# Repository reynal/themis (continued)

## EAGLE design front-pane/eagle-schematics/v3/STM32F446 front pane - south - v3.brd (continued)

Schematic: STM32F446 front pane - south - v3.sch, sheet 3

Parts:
C83, C84, C87, C88, C89, C90, C107, C108, C121, C122, C123, C124, C125, C126: 10u; CPOL2917
C85, C86, C99, C100, C101, C102, C115, C116, C119, C120, C135, C136, C137, C138: 100n; 0805-CAP
C91, C92, C93, C94, C95, C96, C97, C98, C103, C104, C105, C106, C109, C110, C111, C112, C113, C114, C117, C118, C127, C128, C129, C130, C131, C132, C133, C134, C139, C140, C141, C142: 10n; 0805-CAP
D9, D10: CZXR-80RGB03-A; LED4-2.0-D8.0MM
IC22, IC23, IC24, IC25, IC26, IC27, IC28, IC29, IC30, IC31, IC32, IC33: NEOPIXEL-TLC59731DR; SOIC127P600X175-8N
MCP_011, MCP_100: MCP23017; SOIC-28
R130, R131, R132, R133: 1k; R0805
R134, R135, R136, R137, R138, R139, R140, R141, R142, R143, R144, R145, R162, R163, R164, R165, R166, R167, R168, R169, R184, R185, R186, R187, R188, R189, R190, R191, R192, R193, R194, R195: 470; 1206
R146, R147, R148, R150, R151, R152, R154, R155, R156, R158, R159, R160, R170, R171, R172, R174, R175, R176, R178, R179, R180, R181, R182, R183, R196, R197, R198, R200, R201, R202, R204, R205, R206, R208, R209, R210: 100; 1206
R149, R153, R157, R161, R173, R177, R199, R203, R207, R211: 10k; 1206
S14, S15, S16, S17, S18, S19, S20, S21, S22, S23: ENCODER-RGB-SWITCH-NO_NUT; ENCODER_LED_3
SW9, SW10: B3F-1000

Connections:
3V3: C83.+, C84.+, C85.1, C86.1, C87.+, C88.+, C89.+, C90.+, C99.1, C100.1, C101.1, C102.1, C107.+, C108.+, C115.1, C116.1, C119.1, C120.1, C121.+, C122.+, C123.+, C124.+, C125.+, C126.+, C135.1, C136.1, C137.1, C138.1, D9.2 (+), D10.2 (+), IC22.8 (VCC), IC23.8 (VCC), IC24.8 (VCC), IC25.8 (VCC), IC26.8 (VCC), IC27.8 (VCC), IC28.8 (VCC), IC29.8 (VCC), IC30.8 (VCC), IC31.8 (VCC), IC32.8 (VCC), IC33.8 (VCC), MCP_011.9 (VDD), MCP_011.15 (A0), MCP_011.16 (A1), MCP_100.9 (VDD), MCP_100.17 (A2), R130.2, R131.2, R132.2, R133.2, S14.5 (+), S15.5 (+), S16.5 (+), S17.5 (+), S18.5 (+), S19.5 (+), S20.5 (+), S21.5 (+), S22.5 (+), S23.5 (+); also elsewhere on the board
GND: C83.-, C84.-, C85.2, C86.2, C87.-, C88.-, C89.-, C90.-, C91.1, C92.1, C93.1, C94.1, C95.1, C96.1, C97.1, C98.1, C99.2, C100.2, C101.2, C102.2, C103.2, C104.2, C105.2, C106.2, C107.-, C108.-, C109.1, C110.1, C111.1, C112.1, C113.1, C114.1, C115.2, C116.2, C117.2, C118.2, C119.2, C120.2, C121.-, C122.-, C123.-, C124.-, C125.-, C126.-, C127.1, C128.1, C129.1, C130.1, C131.1, C132.1, C133.1, C134.1, C135.2, C136.2, C137.2, C138.2, C139.2, C140.2, C141.2, C142.2, IC22.4 (GND), IC23.4 (GND), IC24.4 (GND), IC25.4 (GND), IC26.4 (GND), IC27.4 (GND), IC28.4 (GND), IC29.4 (GND), IC30.4 (GND), IC31.4 (GND), IC32.4 (GND), IC33.4 (GND), MCP_011.10 (VSS), MCP_011.17 (A2), MCP_100.10 (VSS), MCP_100.15 (A0), MCP_100.16 (A1), R149.2, R153.2, R157.2, R161.2, R173.2, R177.2, R199.2, R203.2, R207.2, R211.2, S14.C, S15.C, S16.C, S17.C, S18.C, S19.C, S20.C, S21.C, S22.C, S23.C, SW9.1, SW9.2, SW10.1, SW10.2; also elsewhere on the board
GPA0_31: MCP_011.21 (GPA0), R140.1, S17.A
GPA0_32: MCP_100.21 (GPA0), R162.1, SW9.3, SW9.4
GPA1_31: MCP_011.22 (GPA1), R141.1, S17.B
GPA1_32: MCP_100.22 (GPA1), R192.1, R199.1, S20.3 (SW)
GPA2_31: MCP_011.23 (GPA2), R145.1, R161.1, S17.3 (SW)
GPA2_32: MCP_100.23 (GPA2), R185.1, S20.B
GPA3_31: MCP_011.24 (GPA3), R163.1, SW10.3, SW10.4
GPA3_32: MCP_100.24 (GPA3), R184.1, S20.A
GPA4_31: MCP_011.25 (GPA4), R144.1, R157.1, S16.3 (SW)
GPA4_32: MCP_100.25 (GPA4), R193.1, R203.1, S21.3 (SW)
GPA5_31: MCP_011.26 (GPA5), R138.1, S16.A
GPA5_32: MCP_100.26 (GPA5), R187.1, S21.B
GPA6_31: MCP_011.27 (GPA6), R139.1, S16.B
GPA6_32: MCP_100.27 (GPA6), R186.1, S21.A
GPA7_31: MCP_011.28 (GPA7), R168.1, R173.1, S18.3 (SW)
GPA7_32: MCP_100.28 (GPA7), R194.1, R207.1, S22.3 (SW)
GPB0_31: MCP_011.1 (GPB0), R165.1, S18.B
GPB0_32: MCP_100.1 (GPB0), R189.1, S22.B
GPB1_31: MCP_011.2 (GPB1), R164.1, S18.A
GPB1_32: MCP_100.2 (GPB1), R188.1, S22.A
GPB2_31: MCP_011.3 (GPB2), R169.1, R177.1, S19.3 (SW)
GPB2_32: MCP_100.3 (GPB2), R191.1, S23.B
GPB3_31: MCP_011.4 (GPB3), R167.1, S19.B
GPB3_32: MCP_100.4 (GPB3), R190.1, S23.A
GPB4_31: MCP_011.5 (GPB4), R166.1, S19.A
GPB4_32: MCP_100.5 (GPB4), R195.1, R211.1, S23.3 (SW)
GPB5_31: MCP_011.6 (GPB5), R134.1, S14.A
GPB5_32: MCP_100.6 (GPB5), R136.1, S15.A
GPB6_31: MCP_011.7 (GPB6), R135.1, S14.B
GPB6_32: MCP_100.7 (GPB6), R137.1, S15.B
GPB7_31: MCP_011.8 (GPB7), R142.1, R149.1, S14.3 (SW)
GPB7_32: MCP_100.8 (GPB7), R143.1, R153.1, S15.3 (SW)
I2C2_SCL: MCP_011.12 (SCL), MCP_100.12 (SCL), R132.1, R133.1; also elsewhere on the board
I2C2_SDA: MCP_011.13 (SDA), MCP_100.13 (SDA), R130.1, R131.1; also elsewhere on the board
INTA_31: MCP_011.20 (INTA); also elsewhere on the board
INTA_32: MCP_100.20 (INTA); also elsewhere on the board
INTB_31: MCP_011.19 (INTB); also elsewhere on the board
INTB_32: MCP_100.19 (INTB); also elsewhere on the board
unnamed: R158.2, S17.1 (-R)
unnamed: R159.2, S17.2 (-G)
unnamed: R160.2, S17.4 (-B)
unnamed: IC25.1 (OUT0), R158.1
unnamed: IC25.2 (OUT1), R159.1
unnamed: IC25.3 (OUT2), R160.1
unnamed: C97.2, R140.2
unnamed: C98.2, R141.2
unnamed: C106.1, R145.2
unnamed: R154.2, S16.1 (-R)
unnamed: R155.2, S16.2 (-G)
unnamed: R156.2, S16.4 (-B)
unnamed: IC24.1 (OUT0), R154.1
unnamed: IC24.2 (OUT1), R155.1
unnamed: IC24.3 (OUT2), R156.1
unnamed: C95.2, R138.2
unnamed: C96.2, R139.2
unnamed: C105.1, R144.2
unnamed: R150.2, S15.1 (-R)
unnamed: R151.2, S15.2 (-G)
unnamed: R152.2, S15.4 (-B)
unnamed: IC23.1 (OUT0), R150.1
unnamed: IC23.2 (OUT1), R151.1
unnamed: IC23.3 (OUT2), R152.1
unnamed: C93.2, R136.2
unnamed: C94.2, R137.2
unnamed: C104.1, R143.2
unnamed: R146.2, S14.1 (-R)
unnamed: R147.2, S14.2 (-G)
unnamed: R148.2, S14.4 (-B)
unnamed: IC22.1 (OUT0), R146.1
unnamed: IC22.2 (OUT1), R147.1
unnamed: IC22.3 (OUT2), R148.1
unnamed: C91.2, R134.2
unnamed: C92.2, R135.2
unnamed: C103.1, R142.2
unnamed: R174.2, S19.1 (-R)
unnamed: R175.2, S19.2 (-G)
unnamed: R176.2, S19.4 (-B)
unnamed: IC29.1 (OUT0), R174.1
unnamed: IC29.2 (OUT1), R175.1
unnamed: IC29.3 (OUT2), R176.1
unnamed: C111.2, R166.2
unnamed: C112.2, R167.2
unnamed: C118.1, R169.2
unnamed: IC27.1 (OUT0), R181.1
unnamed: IC27.2 (OUT1), R182.1
unnamed: IC27.3 (OUT2), R183.1
unnamed: C114.2, R163.2
unnamed: R170.2, S18.1 (-R)
unnamed: R171.2, S18.2 (-G)
unnamed: R172.2, S18.4 (-B)
unnamed: IC28.1 (OUT0), R170.1
unnamed: IC28.2 (OUT1), R171.1
unnamed: IC28.3 (OUT2), R172.1
unnamed: C109.2, R164.2
unnamed: C110.2, R165.2
unnamed: C117.1, R168.2
unnamed: R208.2, S23.1 (-R)
unnamed: R209.2, S23.2 (-G)
unnamed: R210.2, S23.4 (-B)
unnamed: IC33.1 (OUT0), R208.1
unnamed: IC33.2 (OUT1), R209.1
unnamed: IC33.3 (OUT2), R210.1
unnamed: C133.2, R190.2
unnamed: C134.2, R191.2
unnamed: C142.1, R195.2
unnamed: R204.2, S22.1 (-R)
unnamed: R205.2, S22.2 (-G)
unnamed: R206.2, S22.4 (-B)
unnamed: IC32.1 (OUT0), R204.1
unnamed: IC32.2 (OUT1), R205.1
unnamed: IC32.3 (OUT2), R206.1
unnamed: C131.2, R188.2
unnamed: C132.2, R189.2
unnamed: C141.1, R194.2
unnamed: R200.2, S21.1 (-R)
unnamed: R201.2, S21.2 (-G)
unnamed: R202.2, S21.4 (-B)
unnamed: IC31.1 (OUT0), R200.1
unnamed: IC31.2 (OUT1), R201.1
unnamed: IC31.3 (OUT2), R202.1
unnamed: C129.2, R186.2
unnamed: C130.2, R187.2
unnamed: C140.1, R193.2
unnamed: D10.1 (R), R183.2
unnamed: D10.4 (B), R182.2
unnamed: D10.3 (G), R181.2
unnamed: R196.2, S20.1 (-R)
unnamed: R197.2, S20.2 (-G)
unnamed: R198.2, S20.4 (-B)
unnamed: IC30.1 (OUT0), R196.1
unnamed: IC30.2 (OUT1), R197.1
unnamed: IC30.3 (OUT2), R198.1
unnamed: C127.2, R184.2
unnamed: C128.2, R185.2
unnamed: C139.1, R192.2
unnamed: IC26.1 (OUT0), R178.1
unnamed: IC26.2 (OUT1), R179.1
unnamed: IC26.3 (OUT2), R180.1
unnamed: C113.2, R162.2
unnamed: D9.1 (R), R180.2
unnamed: D9.4 (B), R179.2
unnamed: D9.3 (G), R178.2
PIXEL_48: IC33.6 (SDI); also elsewhere on the board
PIXEL_51: IC25.5 (SDO), IC27.6 (SDI)
PIXEL_52: IC24.6 (SDI), IC27.5 (SDO)
PIXEL_53: IC24.5 (SDO), IC28.6 (SDI)
PIXEL_54: IC23.5 (SDO); also elsewhere on the board
PIXEL_55: IC22.5 (SDO), IC23.6 (SDI)
PIXEL_56: IC22.6 (SDI), IC29.5 (SDO)
PIXEL_57: IC28.5 (SDO), IC29.6 (SDI)
PIXEL_61: IC32.6 (SDI), IC33.5 (SDO)
PIXEL_62: IC31.6 (SDI), IC32.5 (SDO)
PIXEL_63: IC30.6 (SDI), IC31.5 (SDO)
PIXEL_64: IC26.6 (SDI), IC30.5 (SDO)
RST: MCP_011.18 (!RESET), MCP_100.18 (!RESET); also elsewhere on the board
SPI3_MOSI: IC25.6 (SDI); also elsewhere on the board

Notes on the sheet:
RGB ENCODER 51
RGB ENCODER 53
RGB ENCODER 54
RGB ENCODER 55
RGB ENCODER 56
RGB ENCODER 57
RGB ENCODER 61
RGB ENCODER 62
RGB ENCODER 63
RGB ENCODER 64
SWITCH RGB 52
SWITCH RGB 65

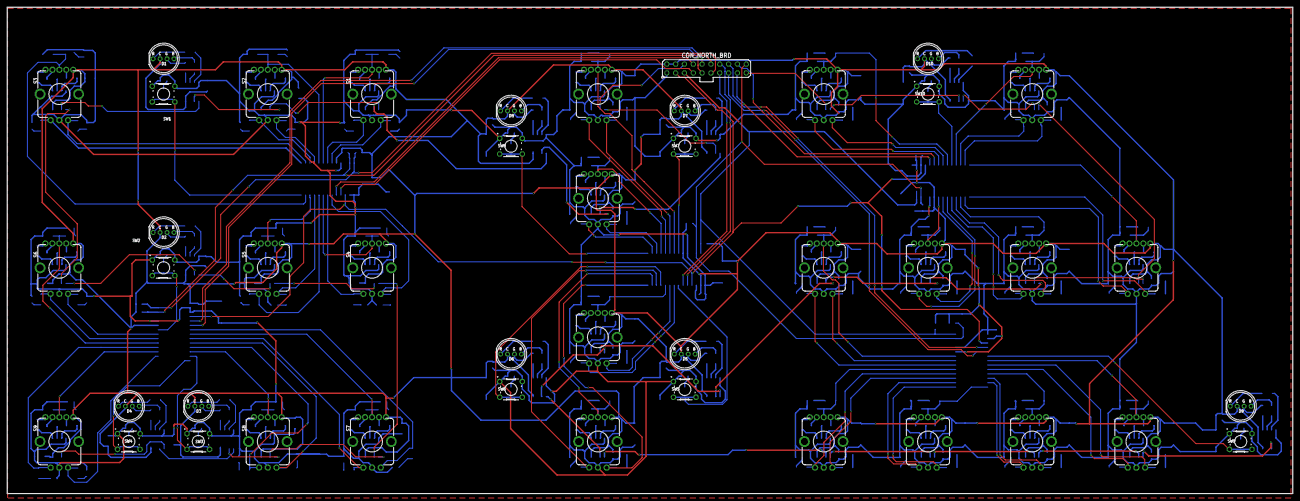
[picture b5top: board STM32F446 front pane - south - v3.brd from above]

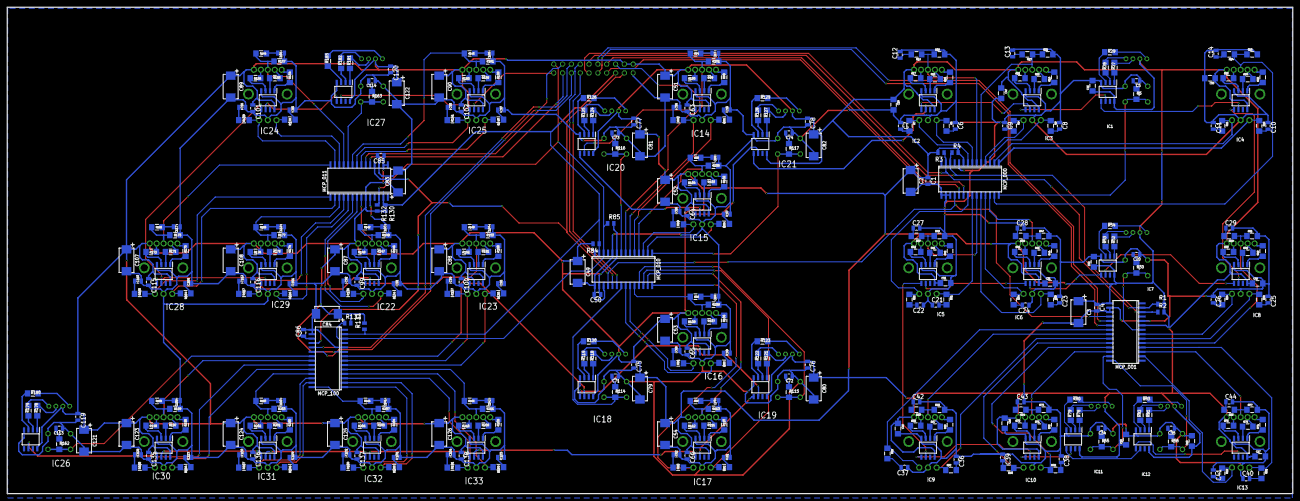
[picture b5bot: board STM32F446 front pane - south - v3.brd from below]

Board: 2 copper layers, 370.0 x 140.0 mm, 435 parts (391 on the bottom side), 406 nets.

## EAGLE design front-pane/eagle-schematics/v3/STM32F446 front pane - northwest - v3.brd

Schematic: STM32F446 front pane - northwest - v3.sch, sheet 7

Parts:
C1, C2, C5, C6, C7, C10, C11, C12, C15: 10n; 0805-CAP
C3, C8, C13: 10u; CPOL2917
C4, C9, C14: 100n; 0805-CAP
ENC_01, ENC_02, ENC_3: ENCODER-RGB-SWITCH-NO_NUT; ENCODER_LED_3
PIXEL_01, PIXEL_02, PIXEL_03: NEOPIXEL-TLC59731DR; SOIC127P600X175-8N
R1, R2, R7, R8, R9, R14, R15, R16, R21: 470; 1206
R3, R4, R5, R10, R11, R12, R17, R18, R19: 100; 1206
R6, R13, R20: 10k; 1206
TFT_EXT_2: MA06-2

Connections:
3V3: C3.+, C4.1, C8.+, C9.1, C13.+, C14.1, ENC_01.5 (+), ENC_02.5 (+), ENC_3.5 (+), PIXEL_01.8 (VCC), PIXEL_02.8 (VCC), PIXEL_03.8 (VCC), TFT_EXT_2.1
ENC_01_A: ENC_01.A, R15.1, TFT_EXT_2.3
ENC_01_B: ENC_01.B, R16.1, TFT_EXT_2.5
ENC_01_SW: ENC_01.3 (SW), R20.1, R21.1, TFT_EXT_2.6
ENC_02_A: ENC_02.A, R8.1, TFT_EXT_2.11
ENC_02_B: ENC_02.B, R9.1, TFT_EXT_2.12
ENC_02_SW: ENC_02.3 (SW), R13.1, R14.1, TFT_EXT_2.4
ENC_03_A: ENC_3.A, R1.1, TFT_EXT_2.10
ENC_03_B: ENC_3.B, R2.1, TFT_EXT_2.8
ENC_03_SW: ENC_3.3 (SW), R6.1, R7.1, TFT_EXT_2.2
GND: C1.1, C2.1, C3.-, C4.2, C5.2, C6.1, C7.1, C8.-, C9.2, C10.2, C11.1, C12.1, C13.-, C14.2, C15.2, ENC_01.C, ENC_02.C, ENC_3.C, PIXEL_01.4 (GND), PIXEL_02.4 (GND), PIXEL_03.4 (GND), R6.2, R13.2, R20.2, TFT_EXT_2.7
unnamed: ENC_01.1 (-R), R17.2
unnamed: ENC_01.2 (-G), R18.2
unnamed: ENC_01.4 (-B), R19.2
unnamed: PIXEL_01.1 (OUT0), R17.1
unnamed: PIXEL_01.2 (OUT1), R18.1
unnamed: PIXEL_01.3 (OUT2), R19.1
unnamed: C11.2, R15.2
unnamed: C12.2, R16.2
unnamed: C15.1, R21.2
unnamed: ENC_02.1 (-R), R10.2
unnamed: ENC_02.2 (-G), R11.2
unnamed: ENC_02.4 (-B), R12.2
unnamed: PIXEL_02.1 (OUT0), R10.1
unnamed: PIXEL_02.2 (OUT1), R11.1
unnamed: PIXEL_02.3 (OUT2), R12.1
unnamed: C6.2, R8.2
unnamed: C7.2, R9.2
unnamed: C10.1, R14.2
unnamed: ENC_3.1 (-R), R3.2
unnamed: ENC_3.2 (-G), R4.2
unnamed: ENC_3.4 (-B), R5.2
unnamed: PIXEL_03.1 (OUT0), R3.1
unnamed: PIXEL_03.2 (OUT1), R4.1
unnamed: PIXEL_03.3 (OUT2), R5.1
unnamed: C1.2, R1.2
unnamed: C2.2, R2.2
unnamed: C5.1, R7.2
PIXEL_02: PIXEL_01.6 (SDI), PIXEL_02.5 (SDO)
PIXEL_03: PIXEL_02.6 (SDI), PIXEL_03.5 (SDO)
PIXEL_IN: PIXEL_03.6 (SDI), TFT_EXT_2.9

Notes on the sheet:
TFT EXTENSION
RGB ENCODER

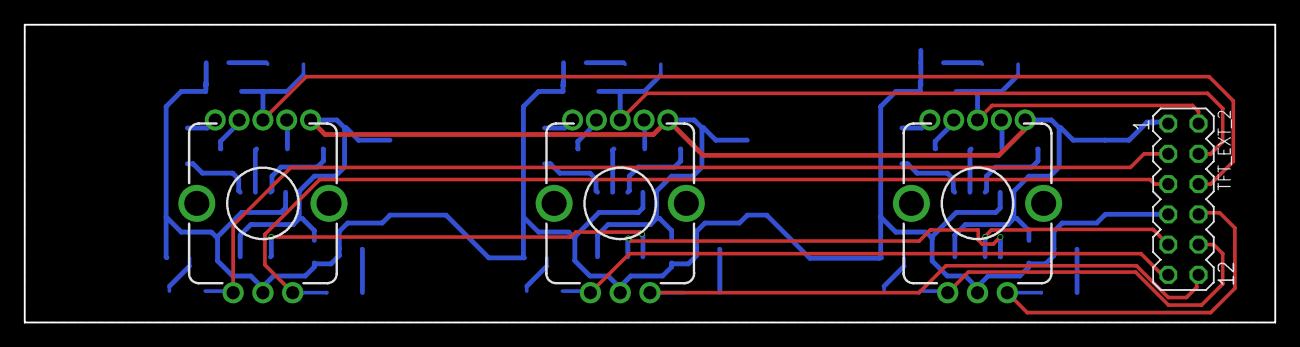
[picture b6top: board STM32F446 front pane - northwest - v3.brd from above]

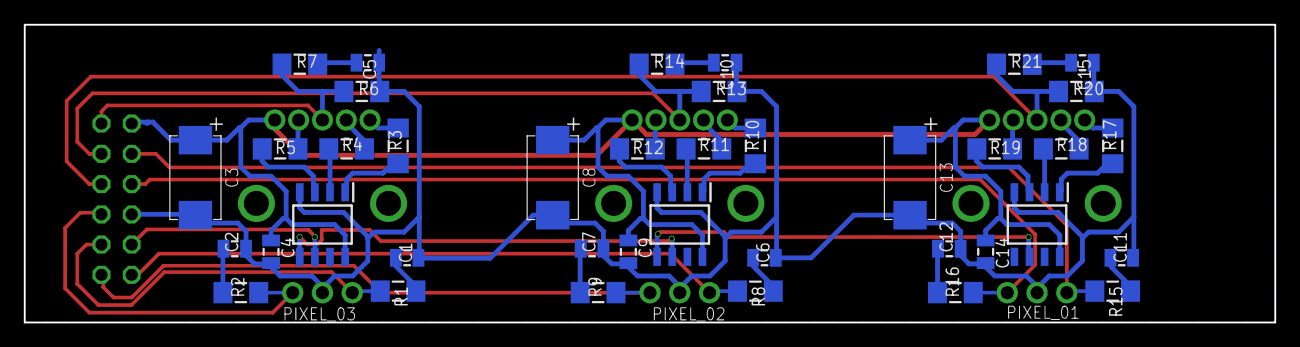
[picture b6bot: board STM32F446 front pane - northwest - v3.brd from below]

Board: 2 copper layers, 105.0 x 25.0 mm, 43 parts (39 on the bottom side), 41 nets.

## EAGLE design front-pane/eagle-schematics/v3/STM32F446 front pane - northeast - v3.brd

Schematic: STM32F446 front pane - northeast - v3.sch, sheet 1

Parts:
0V/5V: SUPPLY; MA04-1
AIN: MA04-1
ANALOG: UART_ANALOG; MA03-1
C1, C6, C7, C8, C9, C10: 0.1uF; C0805
C2: 2.2uF; C0805
C3: 10u; CPOL2917
C4: 100 uF; CPOL2917
C5: 1u; C1206
C11: 1.0uF; C0805
CON_STH_BRD: SOUTH; MA10-2
DISCO: UART_DISCO; MA03-1
F446: STM32F446RCT7; QFP50P1200X1200X160-64N
L1: 1 uH; L0805
LD_3V: LED_3V3; 0805-LED
LD_5V: LED_5V; 0603-LED
LD_GR: LED-0805; 0805-LED
MIDI: UART_MIDI; MA03-1
NRST: SWITCH-SKRKAEE020; SKRKAEE020
R1, R5: 1k; R0805
R2: 100k; R0805
R3: 10K; R0805
R4: 1; R0805
R6: 470; R0805
REG: TLV75533PDBVR; SOT95P280X145-5N
STLINK: STLINK; MA03-2

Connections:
3V3: C4.+, C6.2, C7.2, C8.2, C9.2, C10.2, C11.2, CON_STH_BRD.2, CON_STH_BRD.4, F446.1 (VBAT), F446.13 (VDDA/VREF+), F446.19 (VDD_4), F446.32 (VDD_1), F446.48 (VDD_2), F446.64 (VDD_3), L1.2, R2.1, R5.1, STLINK.1; also elsewhere on the board
5V: 0V/5V.3, 0V/5V.4, C3.+, C5.2, R6.1, REG.1 (IN), REG.3 (EN)
ADC1_IN1: AIN.4, F446.15 (PA1)
ADC1_IN4: AIN.3, F446.20 (PA4)
ADC1_IN10: AIN.2, F446.8 (PC0)
BOOT1: F446.60 (BOOT0), R3.1
GND: 0V/5V.1, 0V/5V.2, AIN.1, ANALOG.1, C1.1, C2.1, C3.-, C4.-, C5.1, C6.1, C7.1, C8.1, C9.1, C10.1, C11.1, CON_STH_BRD.1, DISCO.1, F446.12 (VSSA/VREF-), F446.18 (VSS_4), F446.31 (VSS_1), F446.47 (VSS_2), F446.63 (VSS_3), LD_3V.C, LD_5V.C, LD_GR.C, MIDI.1, NRST.1, R3.2, REG.2 (GND), STLINK.5; also elsewhere on the board
GPIO_EXTI0: F446.5 (PH0-OSC_IN); also elsewhere on the board
GPIO_EXTI1: CON_STH_BRD.17, F446.27 (PB1)
GPIO_EXTI2: F446.10 (PC2); also elsewhere on the board
GPIO_EXTI3: F446.11 (PC3); also elsewhere on the board
GPIO_EXTI4: F446.24 (PC4); also elsewhere on the board
GPIO_EXTI5: F446.25 (PC5); also elsewhere on the board
GPIO_EXTI6: CON_STH_BRD.16, F446.37 (PC6)
GPIO_EXTI7: CON_STH_BRD.13, F446.38 (PC7)
GPIO_EXTI8: CON_STH_BRD.14, F446.39 (PC8)
GPIO_EXTI9: CON_STH_BRD.9, F446.42 (PA9)
GPIO_EXTI10: CON_STH_BRD.10, F446.43 (PA10)
GPIO_EXTI11: CON_STH_BRD.7, F446.44 (PA11)
GPIO_EXTI12: CON_STH_BRD.8, F446.45 (PA12)
GPIO_EXTI13: F446.2 (PC13); also elsewhere on the board
GPIO_EXTI14: CON_STH_BRD.18, F446.35 (PB14)
GPIO_EXTI15: CON_STH_BRD.15, F446.36 (PB15)
I2C1_SCL: F446.61 (PB8); also elsewhere on the board
I2C1_SDA: F446.62 (PB9); also elsewhere on the board
I2C2_SCL: CON_STH_BRD.20, F446.29 (PB10)
I2C2_SDA: CON_STH_BRD.5, F446.53 (PC12)
I2C3_SCL: CON_STH_BRD.12, F446.41 (PA8)
I2C3_SDA: CON_STH_BRD.11, F446.40 (PC9)
unnamed: LD_5V.A, R6.2
unnamed: LD_GR.A, R1.2
unnamed: LD_3V.A, R5.2
unnamed: R4.2, REG.5 (OUT)
unnamed: L1.1, R4.1
NRST: C1.2, F446.7 (NRST), NRST.2, R2.2, STLINK.3
RST: CON_STH_BRD.3, F446.55 (PB3); also elsewhere on the board
SPI1_MOSI: CON_STH_BRD.6, F446.23 (PA7)
SPI2_MOSI: F446.9 (PC1); also elsewhere on the board
SPI3_MOSI: CON_STH_BRD.19, F446.26 (PB0)
SWCLK: F446.49 (PA14), STLINK.4
SWDIO: F446.46 (PA13), STLINK.2
TIM3_CH1: F446.22 (PA6), R1.1
UART4_RX: ANALOG.2, F446.52 (PC11)
UART4_TX: ANALOG.3, F446.14 (PA0)
USART1_RX: DISCO.2, F446.59 (PB7)
USART1_TX: DISCO.3, F446.58 (PB6)
USART2_RX: F446.17 (PA3), MIDI.2
USART2_TX: F446.16 (PA2), MIDI.3
VCAP1: C2.2, F446.30 (VCAP_1)

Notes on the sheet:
STM32F446

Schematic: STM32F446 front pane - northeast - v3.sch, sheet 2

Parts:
C12, C29, C30, C31, C32, C33: 100n; 0805-CAP
C13, C14, C15, C16, C17, C18: 10u; CPOL2917
C19, C20, C21, C22, C23, C24, C25, C26, C27, C28, C34, C35, C36, C37, C38: 10n; 0805-CAP
MCP_111: MCP23017; SOIC-28
PX_CHORUS: NEOPIXEL-TLC59731DR; SOIC127P600X175-8N
PX_DELAY: NEOPIXEL-TLC59731DR; SOIC127P600X175-8N
PX_DRIVE: NEOPIXEL-TLC59731DR; SOIC127P600X175-8N
PX_PORTA: NEOPIXEL-TLC59731DR; SOIC127P600X175-8N
PX_REVERB: NEOPIXEL-TLC59731DR; SOIC127P600X175-8N
R7, R8: 1k; R0805
R9, R10, R11, R12, R13, R14, R15, R16, R17, R18, R19, R20, R21, R22, R23: 470; 1206
R24, R25, R26, R28, R29, R30, R32, R33, R34, R36, R37, R38, R40, R41, R42: 100; 1206
R27, R31, R35, R39, R43: 10k; 1206
S2, S3, S4, S5, S6: ENCODER-RGB-SWITCH-NO_NUT; ENCODER_LED_3

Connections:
3V3: C12.1, C13.+, C14.+, C15.+, C16.+, C17.+, C18.+, C29.1, C30.1, C31.1, C32.1, C33.1, MCP_111.9 (VDD), MCP_111.15 (A0), MCP_111.16 (A1), MCP_111.17 (A2), PX_CHORUS.8 (VCC), PX_DELAY.8 (VCC), PX_DRIVE.8 (VCC), PX_PORTA.8 (VCC), PX_REVERB.8 (VCC), R7.2, R8.2, S2.5 (+), S3.5 (+), S4.5 (+), S5.5 (+), S6.5 (+); also elsewhere on the board
GND: C12.2, C13.-, C14.-, C15.-, C16.-, C17.-, C18.-, C19.1, C20.1, C21.1, C22.1, C23.1, C24.1, C25.1, C26.1, C27.1, C28.1, C29.2, C30.2, C31.2, C32.2, C33.2, C34.2, C35.2, C36.2, C37.2, C38.2, MCP_111.10 (VSS), PX_CHORUS.4 (GND), PX_DELAY.4 (GND), PX_DRIVE.4 (GND), PX_PORTA.4 (GND), PX_REVERB.4 (GND), R27.2, R31.2, R35.2, R39.2, R43.2, S2.C, S3.C, S4.C, S5.C, S6.C; also elsewhere on the board
GPA0_5: MCP_111.21 (GPA0), R20.1, R31.1, S3.3 (SW)
GPA1_5: MCP_111.22 (GPA1), R12.1, S3.B
GPA2_5: MCP_111.23 (GPA2), R11.1, S3.A
GPA3_5: MCP_111.24 (GPA3), R21.1, R35.1, S4.3 (SW)
GPA4_5: MCP_111.25 (GPA4); also elsewhere on the board
GPA5_5: MCP_111.26 (GPA5); also elsewhere on the board
GPA6_5: MCP_111.27 (GPA6); also elsewhere on the board
GPA7_5: MCP_111.28 (GPA7); also elsewhere on the board
GPB0_5: MCP_111.1 (GPB0); also elsewhere on the board
GPB0_42: R14.1, S4.B; also elsewhere on the board
GPB1_5: MCP_111.2 (GPB1); also elsewhere on the board
GPB1_42: R13.1, S4.A; also elsewhere on the board
GPB2_5: MCP_111.3 (GPB2); also elsewhere on the board
GPB2_42: R16.1, S5.B; also elsewhere on the board
GPB3_5: MCP_111.4 (GPB3); also elsewhere on the board
GPB3_42: R15.1, S5.A; also elsewhere on the board
GPB4_5: MCP_111.5 (GPB4); also elsewhere on the board
GPB4_42: R22.1, R39.1, S5.3 (SW); also elsewhere on the board
GPB5_5: MCP_111.6 (GPB5), R19.1, R27.1, S2.3 (SW)
GPB5_42: R18.1, S6.B; also elsewhere on the board
GPB6_5: MCP_111.7 (GPB6), R9.1, S2.A
GPB6_42: R17.1, S6.A; also elsewhere on the board
GPB7_5: MCP_111.8 (GPB7), R10.1, S2.B
GPB7_42: R23.1, R43.1, S6.3 (SW); also elsewhere on the board
GPIO_EXTI4: MCP_111.20 (INTA); also elsewhere on the board
GPIO_EXTI5: MCP_111.19 (INTB); also elsewhere on the board
I2C1_SCL: MCP_111.12 (SCL), R8.1; also elsewhere on the board
I2C1_SDA: MCP_111.13 (SDA), R7.1; also elsewhere on the board
unnamed: R40.2, S6.1 (-R)
unnamed: R41.2, S6.2 (-G)
unnamed: R42.2, S6.4 (-B)
unnamed: PX_DRIVE.1 (OUT0), R40.1
unnamed: PX_DRIVE.2 (OUT1), R41.1
unnamed: PX_DRIVE.3 (OUT2), R42.1
unnamed: C27.2, R17.2
unnamed: C28.2, R18.2
unnamed: C38.1, R23.2
unnamed: R36.2, S5.1 (-R)
unnamed: R37.2, S5.2 (-G)
unnamed: R38.2, S5.4 (-B)
unnamed: PX_CHORUS.1 (OUT0), R36.1
unnamed: PX_CHORUS.2 (OUT1), R37.1
unnamed: PX_CHORUS.3 (OUT2), R38.1
unnamed: C25.2, R15.2
unnamed: C26.2, R16.2
unnamed: C37.1, R22.2
unnamed: R32.2, S4.1 (-R)
unnamed: R33.2, S4.2 (-G)
unnamed: R34.2, S4.4 (-B)
unnamed: PX_DELAY.1 (OUT0), R32.1
unnamed: PX_DELAY.2 (OUT1), R33.1
unnamed: PX_DELAY.3 (OUT2), R34.1
unnamed: C23.2, R13.2
unnamed: C24.2, R14.2
unnamed: C36.1, R21.2
unnamed: R28.2, S3.1 (-R)
unnamed: R29.2, S3.2 (-G)
unnamed: R30.2, S3.4 (-B)
unnamed: PX_REVERB.1 (OUT0), R28.1
unnamed: PX_REVERB.2 (OUT1), R29.1
unnamed: PX_REVERB.3 (OUT2), R30.1
unnamed: C21.2, R11.2
unnamed: C22.2, R12.2
unnamed: C35.1, R20.2
unnamed: R24.2, S2.1 (-R)
unnamed: R25.2, S2.2 (-G)
unnamed: R26.2, S2.4 (-B)
unnamed: PX_PORTA.1 (OUT0), R24.1
unnamed: PX_PORTA.2 (OUT1), R25.1
unnamed: PX_PORTA.3 (OUT2), R26.1
unnamed: C19.2, R9.2
unnamed: C20.2, R10.2
unnamed: C34.1, R19.2
PIXEL_71: PX_CHORUS.6 (SDI), PX_DRIVE.5 (SDO)
PIXEL_72: PX_CHORUS.5 (SDO), PX_DELAY.6 (SDI)
PIXEL_73: PX_DELAY.5 (SDO), PX_REVERB.6 (SDI)
PIXEL_74: PX_PORTA.6 (SDI), PX_REVERB.5 (SDO)
PIXEL_75: PX_PORTA.5 (SDO); also elsewhere on the board
RST: MCP_111.18 (!RESET); also elsewhere on the board
SPI2_MOSI: PX_DRIVE.6 (SDI); also elsewhere on the board

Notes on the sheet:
EFFECTS
RGB ENCODER 71
RGB ENCODER 72
RGB ENCODER 73
RGB ENCODER 74
RGB ENCODER 75

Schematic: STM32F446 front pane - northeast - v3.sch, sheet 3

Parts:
C39, C42, C67, C68, C69, C70, C71, C72, C73, C74: 100n; 0805-CAP
C40, C41, C43, C44, C45, C46, C47, C48, C49, C50: 10u; CPOL2917
C51, C52, C53, C54, C55, C56, C57, C58, C59, C60, C61, C62, C63, C64, C65, C66, C75, C76, C77, C78, C79, C80, C81, C82: 10n; 0805-CAP
CON_TFT_EXT: TFT_EXT; MA06-2
MCP_101, MCP_110: MCP23017; SOIC-28
PX_BF: NEOPIXEL-TLC59731DR; SOIC127P600X175-8N
PX_HUMAN: NEOPIXEL-TLC59731DR; SOIC127P600X175-8N
PX_LATCH: NEOPIXEL-TLC59731DR; SOIC127P600X175-8N
PX_ONOFF: NEOPIXEL-TLC59731DR; SOIC127P600X175-8N
PX_PATTERN: NEOPIXEL-TLC59731DR; SOIC127P600X175-8N
PX_RANGE: NEOPIXEL-TLC59731DR; SOIC127P600X175-8N
PX_RATE: NEOPIXEL-TLC59731DR; SOIC127P600X175-8N
PX_SYNC: NEOPIXEL-TLC59731DR; SOIC127P600X175-8N
R44, R45, R46, R47: 1k; R0805
R48, R49, R50, R51, R52, R53, R54, R55, R56, R57, R58, R59, R60, R61, R62, R63, R64, R65, R66, R67, R68, R69, R70, R71: 470; 1206
R72, R73, R74, R76, R77, R78, R80, R81, R82, R84, R85, R86, R88, R89, R90, R92, R93, R94, R96, R97, R98, R100, R101, R102: 100; 1206
R75, R79, R83, R87, R91, R95, R99, R103: 10k; 1206
S7, S8, S9, S10, S11, S12, S13, S14: ENCODER-RGB-SWITCH-NO_NUT; ENCODER_LED_3

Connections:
3V3: C39.1, C40.+, C41.+, C42.1, C43.+, C44.+, C45.+, C46.+, C47.+, C48.+, C49.+, C50.+, C67.1, C68.1, C69.1, C70.1, C71.1, C72.1, C73.1, C74.1, CON_TFT_EXT.1, MCP_101.9 (VDD), MCP_101.15 (A0), MCP_101.17 (A2), MCP_110.9 (VDD), MCP_110.16 (A1), MCP_110.17 (A2), PX_BF.8 (VCC), PX_HUMAN.8 (VCC), PX_LATCH.8 (VCC), PX_ONOFF.8 (VCC), PX_PATTERN.8 (VCC), PX_RANGE.8 (VCC), PX_RATE.8 (VCC), PX_SYNC.8 (VCC), R44.2, R45.2, R46.2, R47.2, S7.5 (+), S8.5 (+), S9.5 (+), S10.5 (+), S11.5 (+), S12.5 (+), S13.5 (+), S14.5 (+); also elsewhere on the board
GND: C39.2, C40.-, C41.-, C42.2, C43.-, C44.-, C45.-, C46.-, C47.-, C48.-, C49.-, C50.-, C51.1, C52.1, C53.1, C54.1, C55.1, C56.1, C57.1, C58.1, C59.1, C60.1, C61.1, C62.1, C63.1, C64.1, C65.1, C66.1, C67.2, C68.2, C69.2, C70.2, C71.2, C72.2, C73.2, C74.2, C75.2, C76.2, C77.2, C78.2, C79.2, C80.2, C81.2, C82.2, CON_TFT_EXT.7, MCP_101.10 (VSS), MCP_101.16 (A1), MCP_110.10 (VSS), MCP_110.15 (A0), PX_BF.4 (GND), PX_HUMAN.4 (GND), PX_LATCH.4 (GND), PX_ONOFF.4 (GND), PX_PATTERN.4 (GND), PX_RANGE.4 (GND), PX_RATE.4 (GND), PX_SYNC.4 (GND), R75.2, R79.2, R83.2, R87.2, R91.2, R95.2, R99.2, R103.2, S7.C, S8.C, S9.C, S10.C, S11.C, S12.C, S13.C, S14.C; also elsewhere on the board
GPA0_41: MCP_101.21 (GPA0), R71.1, R103.1, S14.3 (SW)
GPA0_42: MCP_110.21 (GPA0), R58.1, S12.A
GPA1_41: MCP_101.22 (GPA1), R70.1, R99.1, S13.3 (SW)
GPA1_42: MCP_110.22 (GPA1), R59.1, S12.B
GPA2_41: MCP_101.23 (GPA2), R60.1, S13.A
GPA2_42: MCP_110.23 (GPA2), R56.1, S11.A
GPA3_41: MCP_101.24 (GPA3), R61.1, S13.B
GPA3_42: MCP_110.24 (GPA3), R57.1, S11.B
GPA4_5: R52.1, S9.A; also elsewhere on the board
GPA4_41: MCP_101.25 (GPA4), R69.1, R95.1, S12.3 (SW)
GPA4_42: MCP_110.25 (GPA4), R68.1, R91.1, S11.3 (SW)
GPA5_5: R53.1, S9.B; also elsewhere on the board
GPA5_41: CON_TFT_EXT.5, MCP_101.26 (GPA5)
GPA5_42: MCP_110.26 (GPA5), R54.1, S10.A
GPA6_5: R66.1, R83.1, S9.3 (SW); also elsewhere on the board
GPA6_41: CON_TFT_EXT.3, MCP_101.27 (GPA6)
GPA6_42: MCP_110.27 (GPA6), R55.1, S10.B
GPA7_5: R65.1, R79.1, S8.3 (SW); also elsewhere on the board
GPA7_41: CON_TFT_EXT.2, MCP_101.28 (GPA7)
GPA7_42: MCP_110.28 (GPA7), R67.1, R87.1, S10.3 (SW)
GPB0_5: R51.1, S8.B; also elsewhere on the board
GPB0_41: CON_TFT_EXT.11, MCP_101.1 (GPB0)
GPB0_42: MCP_110.1 (GPB0); also elsewhere on the board
GPB1_5: R50.1, S8.A; also elsewhere on the board
GPB1_41: CON_TFT_EXT.12, MCP_101.2 (GPB1)
GPB1_42: MCP_110.2 (GPB1); also elsewhere on the board
GPB2_5: R64.1, R75.1, S7.3 (SW); also elsewhere on the board
GPB2_41: CON_TFT_EXT.10, MCP_101.3 (GPB2)
GPB2_42: MCP_110.3 (GPB2); also elsewhere on the board
GPB3_5: R48.1, S7.A; also elsewhere on the board
GPB3_41: CON_TFT_EXT.8, MCP_101.4 (GPB3)
GPB3_42: MCP_110.4 (GPB3); also elsewhere on the board
GPB4_5: R49.1, S7.B; also elsewhere on the board
GPB4_41: CON_TFT_EXT.6, MCP_101.5 (GPB4)
GPB4_42: MCP_110.5 (GPB4); also elsewhere on the board
GPB5_41: CON_TFT_EXT.4, MCP_101.6 (GPB5)
GPB5_42: MCP_110.6 (GPB5); also elsewhere on the board
GPB6_41: MCP_101.7 (GPB6), R62.1, S14.A
GPB6_42: MCP_110.7 (GPB6); also elsewhere on the board
GPB7_41: MCP_101.8 (GPB7), R63.1, S14.B
GPB7_42: MCP_110.8 (GPB7); also elsewhere on the board
GPIO_EXTI0: MCP_101.19 (INTB); also elsewhere on the board
GPIO_EXTI2: MCP_110.19 (INTB); also elsewhere on the board
GPIO_EXTI3: MCP_110.20 (INTA); also elsewhere on the board
GPIO_EXTI13: MCP_101.20 (INTA); also elsewhere on the board
I2C1_SCL: MCP_101.12 (SCL), MCP_110.12 (SCL), R45.1, R47.1; also elsewhere on the board
I2C1_SDA: MCP_101.13 (SDA), MCP_110.13 (SDA), R44.1, R46.1; also elsewhere on the board
unnamed: R96.2, S13.1 (-R)
unnamed: R97.2, S13.2 (-G)
unnamed: R98.2, S13.4 (-B)
unnamed: PX_SYNC.1 (OUT0), R96.1
unnamed: PX_SYNC.2 (OUT1), R97.1
unnamed: PX_SYNC.3 (OUT2), R98.1
unnamed: C63.2, R60.2
unnamed: C64.2, R61.2
unnamed: C81.1, R70.2
unnamed: R92.2, S12.1 (-R)
unnamed: R93.2, S12.2 (-G)
unnamed: R94.2, S12.4 (-B)
unnamed: PX_RANGE.1 (OUT0), R92.1
unnamed: PX_RANGE.2 (OUT1), R93.1
unnamed: PX_RANGE.3 (OUT2), R94.1
unnamed: C61.2, R58.2
unnamed: C62.2, R59.2
unnamed: C80.1, R69.2
unnamed: R88.2, S11.1 (-R)
unnamed: R89.2, S11.2 (-G)
unnamed: R90.2, S11.4 (-B)
unnamed: PX_HUMAN.1 (OUT0), R88.1
unnamed: PX_HUMAN.2 (OUT1), R89.1
unnamed: PX_HUMAN.3 (OUT2), R90.1
unnamed: C59.2, R56.2
unnamed: C60.2, R57.2
unnamed: C79.1, R68.2
unnamed: R84.2, S10.1 (-R)
unnamed: R85.2, S10.2 (-G)
unnamed: R86.2, S10.4 (-B)
unnamed: PX_PATTERN.1 (OUT0), R84.1
unnamed: PX_PATTERN.2 (OUT1), R85.1
unnamed: PX_PATTERN.3 (OUT2), R86.1
unnamed: C57.2, R54.2
unnamed: C58.2, R55.2
unnamed: C78.1, R67.2
unnamed: R80.2, S9.1 (-R)
unnamed: R81.2, S9.2 (-G)
unnamed: R82.2, S9.4 (-B)
unnamed: PX_LATCH.1 (OUT0), R80.1
unnamed: PX_LATCH.2 (OUT1), R81.1
unnamed: PX_LATCH.3 (OUT2), R82.1
unnamed: C55.2, R52.2
unnamed: C56.2, R53.2
unnamed: C77.1, R66.2
unnamed: R100.2, S14.1 (-R)
unnamed: R101.2, S14.2 (-G)
unnamed: R102.2, S14.4 (-B)
unnamed: PX_RATE.1 (OUT0), R100.1
unnamed: PX_RATE.2 (OUT1), R101.1
unnamed: PX_RATE.3 (OUT2), R102.1
unnamed: C65.2, R62.2
unnamed: C66.2, R63.2
unnamed: C82.1, R71.2
unnamed: R76.2, S8.1 (-R)
unnamed: R77.2, S8.2 (-G)
unnamed: R78.2, S8.4 (-B)
unnamed: PX_BF.1 (OUT0), R76.1
unnamed: PX_BF.2 (OUT1), R77.1
unnamed: PX_BF.3 (OUT2), R78.1
unnamed: C53.2, R50.2
unnamed: C54.2, R51.2
unnamed: C76.1, R65.2
unnamed: R72.2, S7.1 (-R)
unnamed: R73.2, S7.2 (-G)
unnamed: R74.2, S7.4 (-B)
unnamed: PX_ONOFF.1 (OUT0), R72.1
unnamed: PX_ONOFF.2 (OUT1), R73.1
unnamed: PX_ONOFF.3 (OUT2), R74.1
unnamed: C51.2, R48.2
unnamed: C52.2, R49.2
unnamed: C75.1, R64.2
PIXEL_75: PX_ONOFF.6 (SDI); also elsewhere on the board
PIXEL_81: CON_TFT_EXT.9, PX_RATE.5 (SDO)
PIXEL_82: PX_RATE.6 (SDI), PX_SYNC.5 (SDO)
PIXEL_83: PX_RANGE.5 (SDO), PX_SYNC.6 (SDI)
PIXEL_84: PX_HUMAN.5 (SDO), PX_RANGE.6 (SDI)
PIXEL_85: PX_HUMAN.6 (SDI), PX_PATTERN.5 (SDO)
PIXEL_86: PX_LATCH.5 (SDO), PX_PATTERN.6 (SDI)
PIXEL_87: PX_BF.5 (SDO), PX_LATCH.6 (SDI)
PIXEL_88: PX_BF.6 (SDI), PX_ONOFF.5 (SDO)
RST: MCP_101.18 (!RESET), MCP_110.18 (!RESET); also elsewhere on the board

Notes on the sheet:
ARP
RGB ENCODER 81
RGB ENCODER 82
RGB ENCODER 83
RGB ENCODER 84
RGB ENCODER 85
RGB ENCODER 86
RGB ENCODER 87
RGB ENCODER 88
MCP 41 & 42

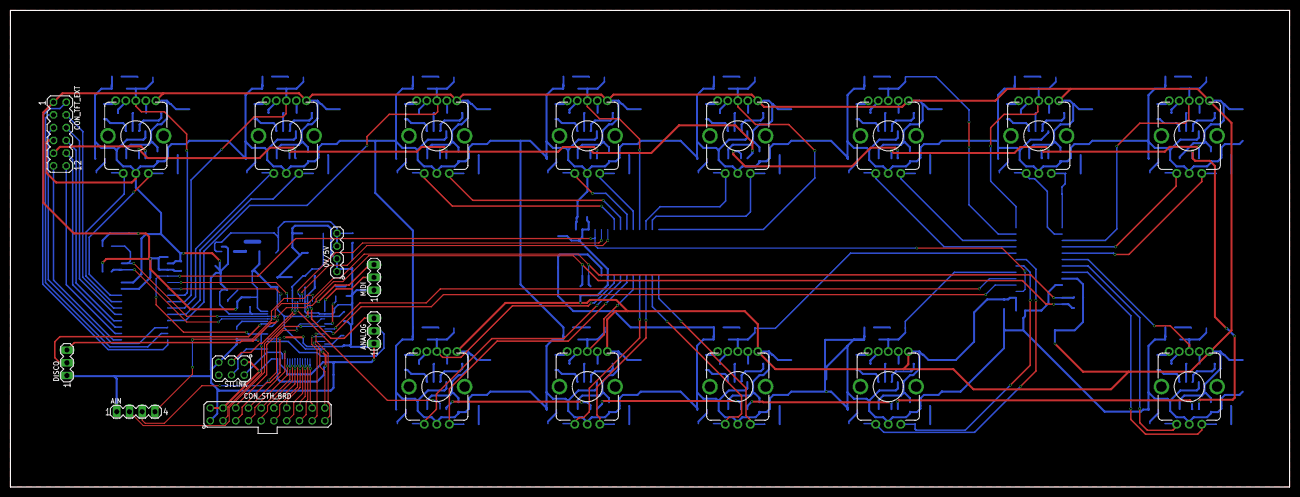
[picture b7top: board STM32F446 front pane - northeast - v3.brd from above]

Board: 2 copper layers, 255.0 x 95.0 mm, 229 parts (208 on the bottom side), 227 nets.

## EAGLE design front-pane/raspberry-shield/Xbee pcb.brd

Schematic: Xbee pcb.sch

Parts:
D_ASSOC: HLMP6
D_IN: HLMP6
D_OUT: HLMP6
D_POWER: HLMP6
PCB1: RPI3RPI3; RPI3
R6, R7, R8, R9, R10: 330; 0207/7
RSSI: HLMP6
XB1: XBEE

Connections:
ASSOC: R10.2, XB1.15 (ASSOC/AD5/DIO5)
DIN: D_IN.K, PCB1.P$8 (GPIO14), XB1.3 (DIN/!CONFIG)
DOUT: D_OUT.K, PCB1.P$10 (GPIO15), XB1.2 (DOUT)
GND: D_ASSOC.K, D_POWER.K, PCB1.P$9 (GND), RSSI.K, XB1.10 (GND)
unnamed: PCB1.P$17 (3V3), XB1.5 (!RESET)
unnamed: D_ASSOC.A, R10.1
unnamed: D_OUT.A, R7.1
unnamed: D_POWER.A, R6.1
unnamed: R9.1, RSSI.A
unnamed: D_IN.A, R8.1
RSSI: R9.2, XB1.6 (PWM0/RSSI)
VCC: PCB1.P$1 (3V3), R6.2, R7.2, R8.2, XB1.1 (VCC)

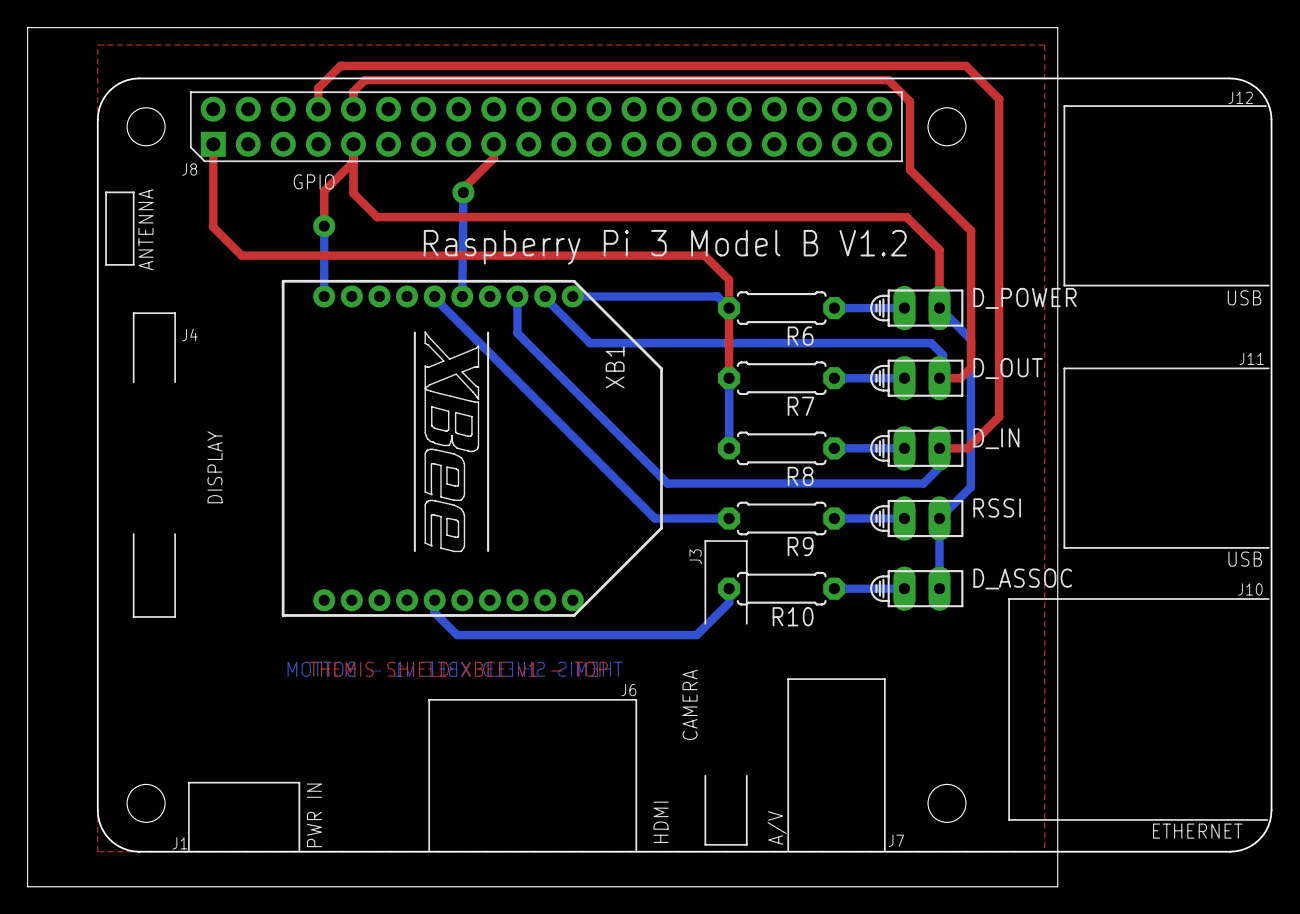
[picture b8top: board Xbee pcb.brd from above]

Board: 2 copper layers, 90.1 x 62.2 mm, 12 parts (0 on the bottom side), 12 nets.
